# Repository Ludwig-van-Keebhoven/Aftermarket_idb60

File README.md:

# Aftermarket idb60 pcb

## Introduction
The aftermarket Alps pcb for idb60 that no one asked for but got. It supports Alps SKCL/SKCM and SKCP (pcb mount). Mx stabilisers are used for SKCL/SKCM, costar pcb mount can be used for both. It also comes with USB-C and have ESD protection.

## Supported layouts

## Contributors
* Pngu from who knows where. Voted sexiest man alive three years in a row!
* Me, Myself, and I

## Previews

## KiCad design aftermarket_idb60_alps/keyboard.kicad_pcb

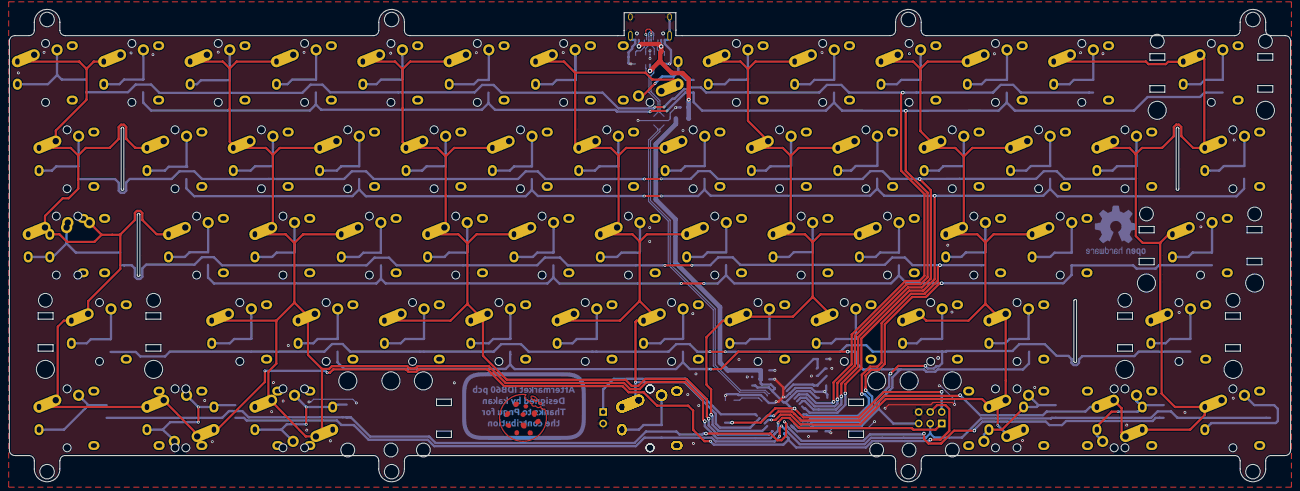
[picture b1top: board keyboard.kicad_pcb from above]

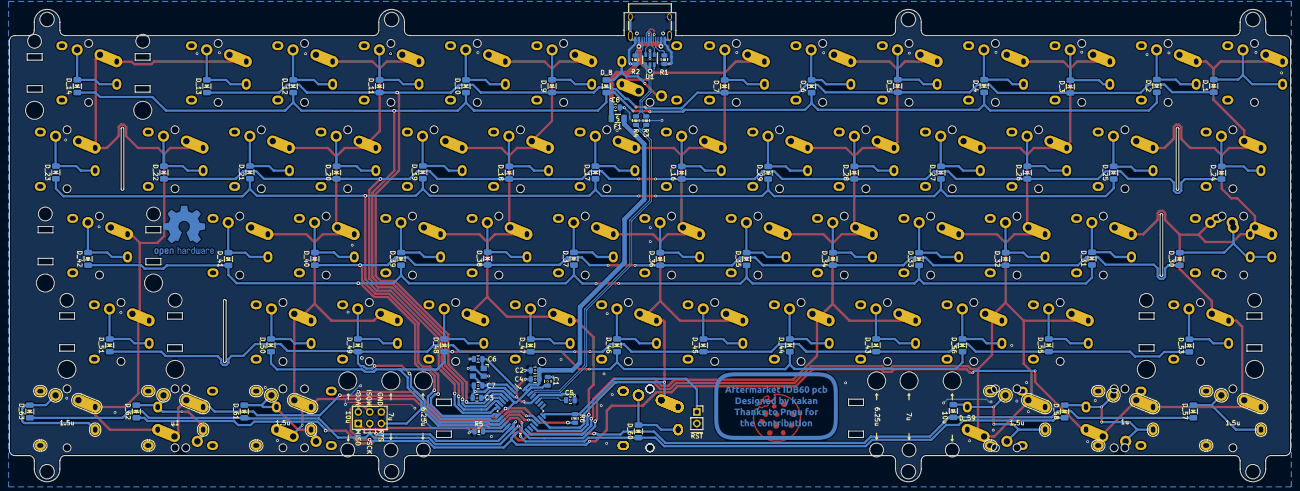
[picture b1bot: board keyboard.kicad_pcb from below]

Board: 2 copper layers, 282.6 x 104.2 mm, 150 parts (81 on the bottom side), 93 nets.

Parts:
C1, C2, C3: 0.1uF; C_0805
C4: 10uF; C_0805
C5: 1uF; C_0805
C6, C7: 22pF; C_0805
C8: 100nF; C_0805
D_1, D_2, D_3, D_4, D_5, D_6, D_7, D_8, D_9, D_10, D_11, D_12, D_13, D_14, D_16, D_17, D_18, D_19, D_20, D_21, D_22, D_23, D_24, D_25, D_26, D_27, D_28, D_29, D_30, D_31, D_32, D_33, D_34, D_35, D_36, D_37, D_38, D_39, D_40, D_41, D_42, D_43, D_44, D_45, D_46, D_47, D_48, D_49, D_50, D_51, D_53, D_55, D_56, D_57, D_58, D_59, D_60, D_61, D_62, D_63: D; D_1206
F1: 500mA; Fuse_1206
H2: kakan_logo_Cu
H3: kakan_logo_F.Silk
J1: USB_C_Receptacle_USB2.0; USB_C_Receptacle_HRO_TYPE-C-31-M-12
J2: AVR-ISP-6; AVR_ICSP_3x2
JP1: ~RST~; PinSocket_1x02_P2.54mm_Vertical
K_1, K_2, K_3, K_4, K_5, K_6, K_7, K_9, K_10, K_11, K_12, K_13, K_17, K_18, K_19, K_20, K_21, K_22, K_23, K_26, K_27, K_28, K_29, K_30, K_33, K_34, K_35, K_36, K_37, K_38, K_39, K_40, K_41, K_42, K_43, K_47, K_48, K_49, K_50, K_51, K_52, K_53, K_54, K_61, K_62: KEYSW; ALPS_SKCM-P_1U
K_8: KEYSW; ALPS_SKCM-P_1U_USB
K_15: KEYSW; ALPS_SKCM-P_2U
K_24, K_25, K_67, K_71: KEYSW; ALPS_SKCM-P_1.5U
K_31: KEYSW; ALPS_SKCM-P_1.75U_L3
K_32, K_65, K_73: KEYSW; ALPS_SKCM-P_1.25U
K_45, K_59: KEYSW; ALPS_SKCM-P_2.25U
K_56: KEYSW; ALPS_SKCM-P_2.75U
K_63, K_66, K_72, K_75: KEYSW; ALPS_SKCM-P_1.5U_SILK
K_64, K_74: KEYSW; ALPS_SKCM-P_1U_SILK
K_68: KEYSW; ALPS_SKCM-P_10U
K_69: KEYSW; ALPS_SKCM-P_7U
K_70: KEYSW; ALPS_SKCM-P_6.25U
R1, R2: 5.1k; R_0805
R3, R4: 22; R_0805
R5, R6: 10k; R_0805
U1: USBLC6-2SC6; SOT-23-6
U2: ATMEGA32U2; TQFP-32_7x7mm_P0.8mm
X1: XTAL_GND; FA-238

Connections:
/DR+: R3.1, U2.29
/DR-: R4.1, U2.30
D+: R3.2, U1.6
D-: R4.2, U1.4
DN-: J1.A7, J1.B7, U1.3
DP+: J1.A6, J1.B6, U1.1
GND: C1.2, C2.2, C3.2, C4.2, C5.2, C6.2, C7.2, C8.2, J1.A1, J1.A12, J1.B1, J1.B12, J1.S1, J2.6, JP1.2, R1.1, R2.2, R5.1, U1.2, U2.3, U2.28, X1.3
MISO: J2.1, K_3.1, K_4.1, K_27.1, K_28.1, K_34.1, K_35.1, K_61.1, K_62.1, K_66.1, K_67.1, U2.17
MOSI: J2.4, K_1.1, K_2.1, K_25.1, K_26.1, K_31.1, K_32.1, K_33.1, K_59.1, K_63.1, K_64.1, K_65.1, U2.16
unnamed: C5.1, U2.27
unnamed: C6.1, U2.1, X1.1
unnamed: C7.1, U2.2, X1.2
unnamed: D_1.2, K_1.2
unnamed: D_2.2, K_2.2
unnamed: D_3.2, K_3.2
unnamed: D_4.2, K_4.2
unnamed: D_5.2, K_5.2
unnamed: D_6.2, K_6.2
unnamed: D_7.2, K_7.2
unnamed: D_8.2, K_8.2
unnamed: D_9.2, K_9.2
unnamed: D_10.2, K_10.2
unnamed: D_11.2, K_11.2
unnamed: D_12.2, K_12.2
unnamed: D_13.2, K_13.2
unnamed: D_14.2, K_15.2
unnamed: D_16.2, K_17.2
unnamed: D_17.2, K_18.2
unnamed: D_18.2, K_19.2
unnamed: D_19.2, K_20.2
unnamed: D_20.2, K_21.2
unnamed: D_21.2, K_22.2
unnamed: D_22.2, K_23.2
unnamed: D_23.2, K_24.2
unnamed: D_24.2, K_25.2
unnamed: D_25.2, K_26.2
unnamed: D_26.2, K_27.2
unnamed: D_27.2, K_28.2
unnamed: D_28.2, K_29.2
unnamed: D_29.2, K_30.2
unnamed: D_30.2, K_31.2, K_32.2
unnamed: D_31.2, K_33.2
unnamed: D_32.2, K_34.2
unnamed: D_33.2, K_35.2
unnamed: D_34.2, K_36.2
unnamed: D_35.2, K_37.2
unnamed: D_36.2, K_38.2
unnamed: D_37.2, K_39.2
unnamed: D_38.2, K_40.2
unnamed: D_39.2, K_41.2
unnamed: D_40.2, K_42.2
unnamed: D_41.2, K_43.2
unnamed: D_42.2, K_45.2
unnamed: D_43.2, K_47.2
unnamed: D_44.2, K_48.2
unnamed: D_45.2, K_49.2
unnamed: D_46.2, K_50.2
unnamed: D_47.2, K_51.2
unnamed: D_48.2, K_52.2
unnamed: D_49.2, K_53.2
unnamed: D_50.2, K_54.2
unnamed: D_51.2, K_56.2
unnamed: D_53.2, K_59.2
unnamed: D_55.2, K_61.2
unnamed: D_56.2, K_62.2
unnamed: D_57.2, K_63.2
unnamed: D_58.2, K_64.2, K_65.2
unnamed: D_59.2, K_66.2, K_67.2
unnamed: D_60.2, K_68.2, K_69.2, K_70.2
unnamed: D_61.2, K_71.2, K_72.2
unnamed: D_62.2, K_73.2, K_74.2
unnamed: D_63.2, K_75.2
unnamed: J1.A5, R1.2
unnamed: J1.B5, R2.1
unnamed: JP1.1, R6.1, U2.24
unnamed: R5.2, U2.13
RTS: D_44.1, D_46.1, D_48.1, D_50.1, D_56.1, J2.5, U2.12
SCK: D_58.1, D_60.1, D_61.1, D_63.1, J2.3, U2.15
VBUS: C8.1, F1.2, J1.A4, J1.A9, J1.B4, J1.B9, U1.5
VCC: C1.1, C2.1, C3.1, C4.1, F1.1, J2.2, R6.2, U2.4, U2.31, U2.32
col2: K_5.1, K_6.1, K_29.1, K_30.1, K_36.1, K_37.1, K_47.1, K_48.1, U2.18
col3: K_7.1, K_8.1, K_17.1, K_18.1, K_38.1, K_39.1, K_49.1, K_50.1, K_68.1, K_69.1, K_70.1, U2.23
col4: K_9.1, K_10.1, K_19.1, K_20.1, K_40.1, K_41.1, K_51.1, K_52.1, U2.20
col5: K_11.1, K_12.1, K_21.1, K_22.1, K_42.1, K_43.1, K_53.1, K_54.1, K_71.1, K_72.1, U2.21
col6: K_13.1, K_15.1, K_23.1, K_24.1, K_45.1, K_56.1, K_73.1, K_74.1, K_75.1, U2.22
row0: D_1.1, D_3.1, D_5.1, D_7.1, D_9.1, D_11.1, D_13.1, U2.5
row1: D_2.1, D_4.1, D_6.1, D_8.1, D_10.1, D_12.1, D_14.1, U2.6
row2: D_16.1, D_18.1, D_20.1, D_22.1, D_24.1, D_26.1, D_28.1, U2.7
row3: D_17.1, D_19.1, D_21.1, D_23.1, D_25.1, D_27.1, D_29.1, U2.8
row4: D_30.1, D_32.1, D_34.1, D_36.1, D_38.1, D_40.1, U2.9
row5: D_31.1, D_33.1, D_35.1, D_37.1, D_39.1, D_41.1, D_42.1, U2.10
row6: D_43.1, D_45.1, D_47.1, D_49.1, D_51.1, D_53.1, D_55.1, U2.11
row8: D_57.1, D_59.1, D_62.1, U2.14

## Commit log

2020-11-11 Kicad files
2020-11-12 pictures
    layout and boardview
